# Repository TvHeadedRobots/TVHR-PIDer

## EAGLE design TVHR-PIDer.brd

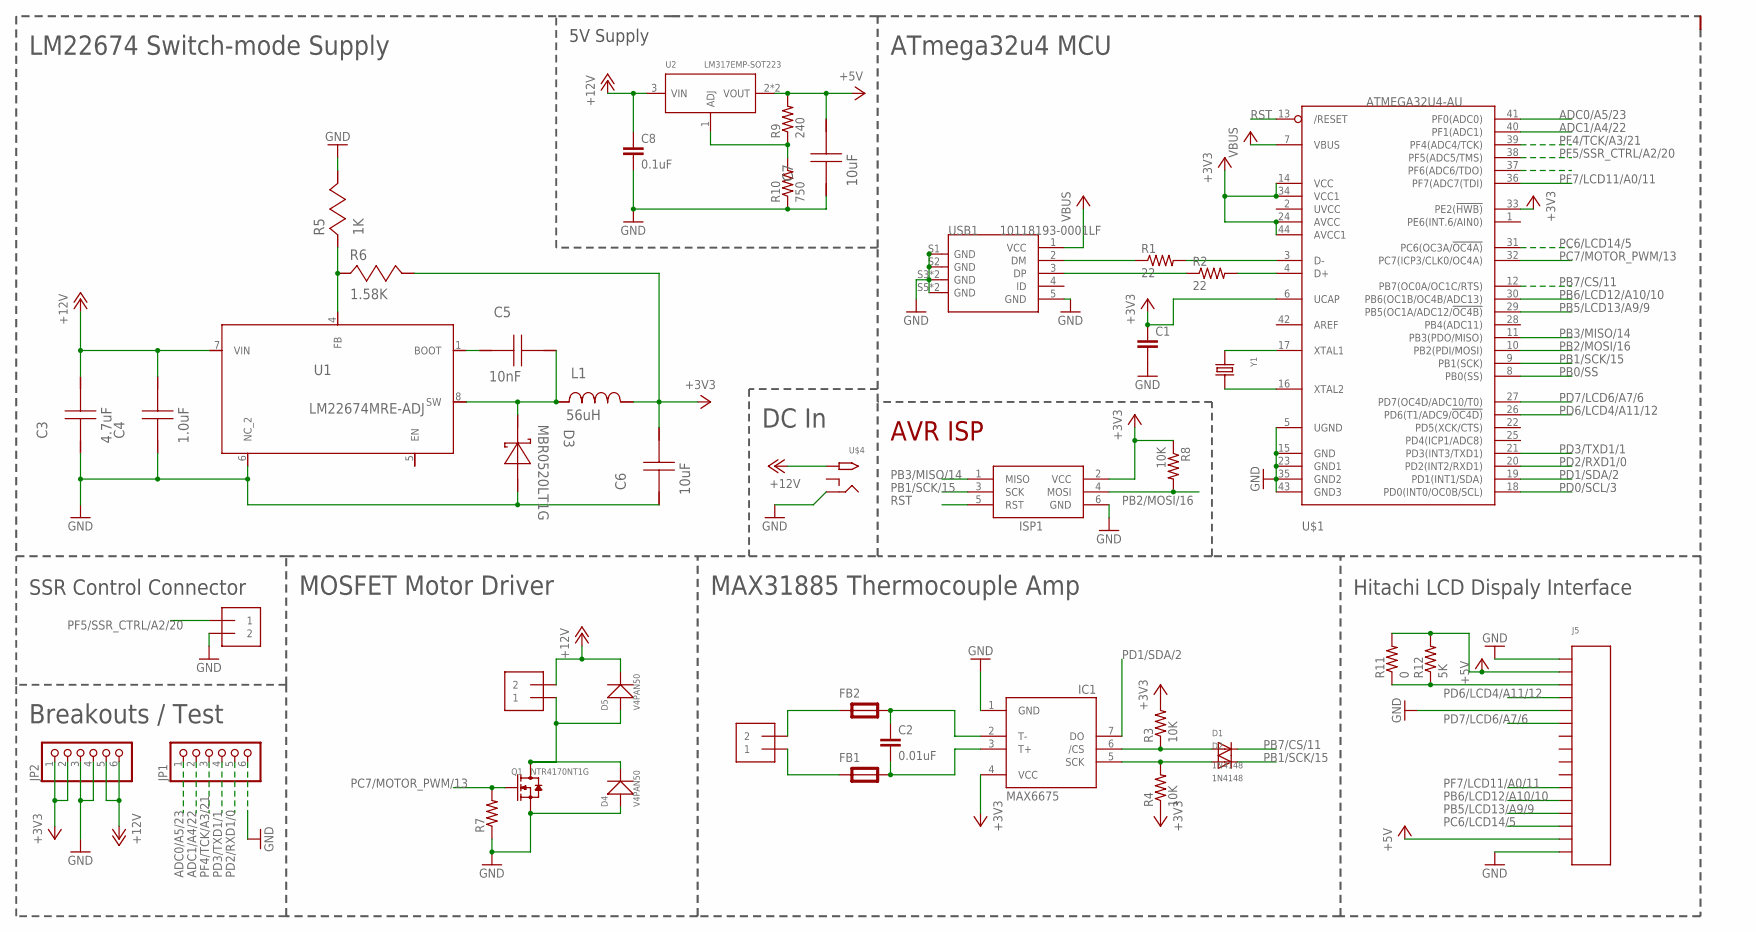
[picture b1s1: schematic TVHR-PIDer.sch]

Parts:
C1: C-EUC0603; C0603
C2: 0.01uF; C0603
C3: 4.7uF; 0805
C4: 1.0uF; 0603
C5: 10nF; 0805
C6, C7: 10uF; 0805
C8: 0.1uF; C0603
D1, D2: 1N4148; SOD-323F
D3: MBR0520LT1G; SOD-123
D4, D5: V4PAN50; SMD-DIODE-DO221BC-2
FB1, FB2: FERRITE-BEAD; R0805
IC1: MAX6675; SO08
ISP1: AVRISP-BOX
J2, J3, J4: 1X2-3.5MM
J5: 16X2-CHAR-LCD-MODULE; H16-2.54
JP1, JP2: PINHD-1X6; 1X06
L1: 56uH; ELL6UH
Q1: NTR4170NT1G; SOT-23
R1, R2: 22; R0603
R3, R4, R8: 10K; R0603
R5: 1K; 0805
R6: 1.58K; 0805
R7: R-US_R0603; R0603
R9: 240; R0603
R10: 750; R0603
R11: 0; R0603
R12: 5K; R0603
U1: LM22674MRE-ADJ; MRA08B
U2: LM317EMP-SOT223; SOT-223
U$1: ATMEGA32U4-AU; TQFP44
U$4: 2.1MMJACKTHM; PJ-102A
USB1: 10118193-0001LF; MICRO-USB5+6P-SMD-0.65-B
Y1: SMD-XTAL--ABM3B-8.000MHZ-B2-T; XTAL-SMD-5.0X3.2X1.1MM

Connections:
+3V3: C1.1, C6.1, IC1.4 (VCC), ISP1.2 (VCC), JP2.1, JP2.2, L1.2, R3.2, R4.1, R6.1, R8.1, U$1.6 (UCAP), U$1.14 (VCC), U$1.24 (AVCC), U$1.33 (PE2(!HWB)), U$1.34 (VCC1), U$1.44 (AVCC1)
+5V: C7.1, J5.2, J5.15, R9.2, R11.2, R12.2, U2.2 (VOUT), U2.TER (VOUT)
+12V: C3.1, C4.1, C8.1, D5.P$2 (-), J4.2, JP2.5, JP2.6, U1.7 (VIN), U2.3 (VIN), U$4.TIP
ADC0/A5/23: JP1.1, U$1.41 (PF0(ADC0))
ADC1/A4/22: JP1.2, U$1.40 (PF1(ADC1))
GND: C1.2, C3.2, C4.2, C6.2, C7.2, C8.2, D3.2 (A), D4.P$1 (+), IC1.1 (GND), ISP1.6 (GND), J3.2, J5.1, J5.5, J5.16, JP1.6, JP2.3, JP2.4, Q1.2 (S), R5.1, R7.1, R10.1, U1.6 (NC_2), U$1.5 (UGND), U$1.15 (GND), U$1.23 (GND1), U$1.35 (GND2), U$1.43 (GND3), U$4.RING, USB1.5 (GND), USB1.S1 (GND), USB1.S2 (GND), USB1.S3 (GND), USB1.S4 (GND), USB1.S5 (GND), USB1.S6 (GND)
unnamed: R1.2, U$1.3 (D-)
unnamed: R1.1, USB1.2 (DM)
unnamed: R2.1, USB1.3 (DP)
unnamed: U$1.17 (XTAL1), Y1.P$1 (1)
unnamed: R2.2, U$1.4 (D+)
unnamed: U$1.16 (XTAL2), Y1.P$2 (2)
unnamed: C2.1, FB2.2, IC1.2 (T-)
unnamed: C2.2, FB1.2, IC1.3 (T+)
unnamed: R9.1, R10.2, U2.1 (ADJ)
unnamed: FB2.1, J2.2
unnamed: FB1.1, J2.1
unnamed: R5.2, R6.2, U1.4 (FB)
unnamed: J5.3, R11.1, R12.1
unnamed: C5.2, U1.1 (BOOT)
unnamed: C5.1, D3.1 (K), L1.1, U1.8 (SW)
unnamed: D4.P$2 (-), D5.P$1 (+), J4.1, Q1.3 (D)
PB0/SS: U$1.8 (PB0(SS))
PB1/SCK/15: D2.A, D2.C, IC1.5 (SCK), ISP1.3 (SCK), R4.2, U$1.9 (PB1(SCK))
PB2/MOSI/16: ISP1.4 (MOSI), R8.2, U$1.10 (PB2(PDI/MOSI))
PB3/MISO/14: ISP1.1 (MISO), U$1.11 (PB3(PDO/MISO))
PB5/LCD13/A9/9: J5.13, U$1.29 (PB5(OC1A/ADC12/!OC4B))
PB6/LCD12/A10/10: J5.12, U$1.30 (PB6(OC1B/OC4B/ADC13))
PB7/CS/11: D1.A, D1.C, IC1.6 (/CS), R3.1, U$1.12 (PB7(OC0A/OC1C/RTS))
PC6/LCD14/5: J5.14, U$1.31 (PC6(OC3A/!OC4A))
PC7/MOTOR_PWM/13: Q1.1 (G), R7.2, U$1.32 (PC7(ICP3/CLK0/OC4A))
PD0/SCL/3: U$1.18 (PD0(INT0/OC0B/SCL))
PD1/SDA/2: IC1.7 (DO), U$1.19 (PD1(INT1/SDA))
PD2/RXD1/0: JP1.5, U$1.20 (PD2(INT2/RXD1))
PD3/TXD1/1: JP1.4, U$1.21 (PD3(INT3/TXD1))
PD6/LCD4/A11/12: J5.4, U$1.26 (PD6(T1/ADC9/!OC4D))
PD7/LCD6/A7/6: J5.6, U$1.27 (PD7(OC4D/ADC10/T0))
PF4/TCK/A3/21: JP1.3, U$1.39 (PF4(ADC4/TCK))
PF5/SSR_CTRL/A2/20: J3.1, U$1.38 (PF5(ADC5/TMS))
PF7/LCD11/A0/11: J5.11, U$1.36 (PF7(ADC7(TDI))
RST: ISP1.5 (RST), U$1.13 (/RESET)
VBUS: U$1.7 (VBUS), USB1.1 (VCC)

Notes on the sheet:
ATmega32u4 MCU
Hitachi LCD Dispaly Interface
MAX31885 Thermocouple Amp
SSR Control Connector
LM22674 Switch-mode Supply
MOSFET Motor Driver
AVR ISP
Breakouts / Test
DC In
5V Supply

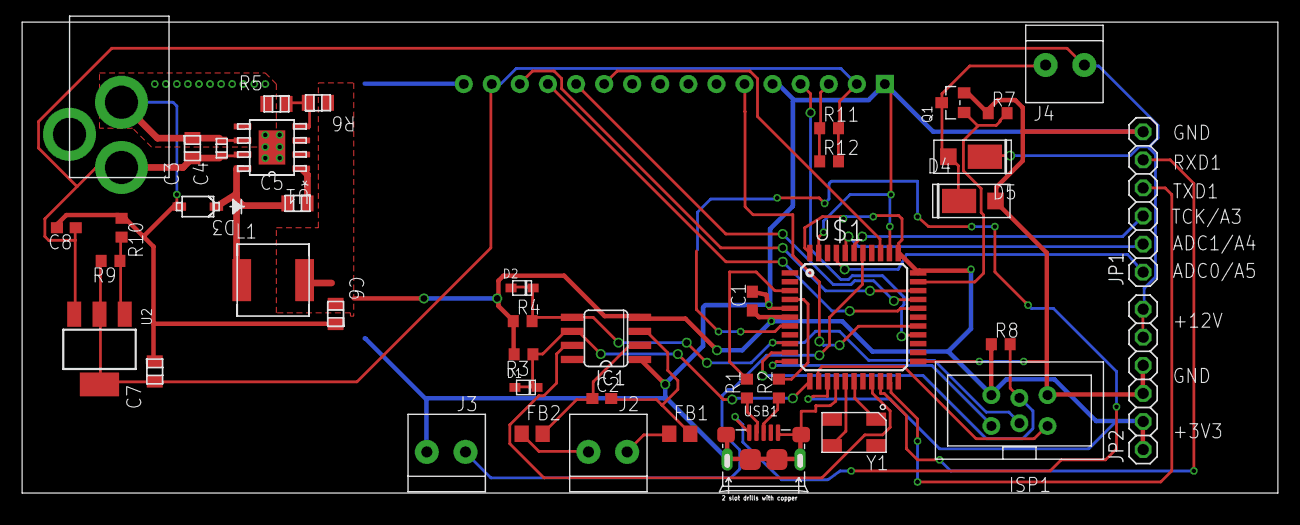
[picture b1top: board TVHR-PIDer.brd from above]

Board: 2 copper layers, 113.1 x 43.0 mm, 43 parts (1 on the bottom side), 40 nets.

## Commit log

2016-02-07 :confetti_ball: Added .gitattributes & .gitignore files
2016-05-01 Added files
